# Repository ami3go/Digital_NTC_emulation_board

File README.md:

# Digital_NTC_emulation_board
 Emulation NTC by using digital potentiomener AD5235

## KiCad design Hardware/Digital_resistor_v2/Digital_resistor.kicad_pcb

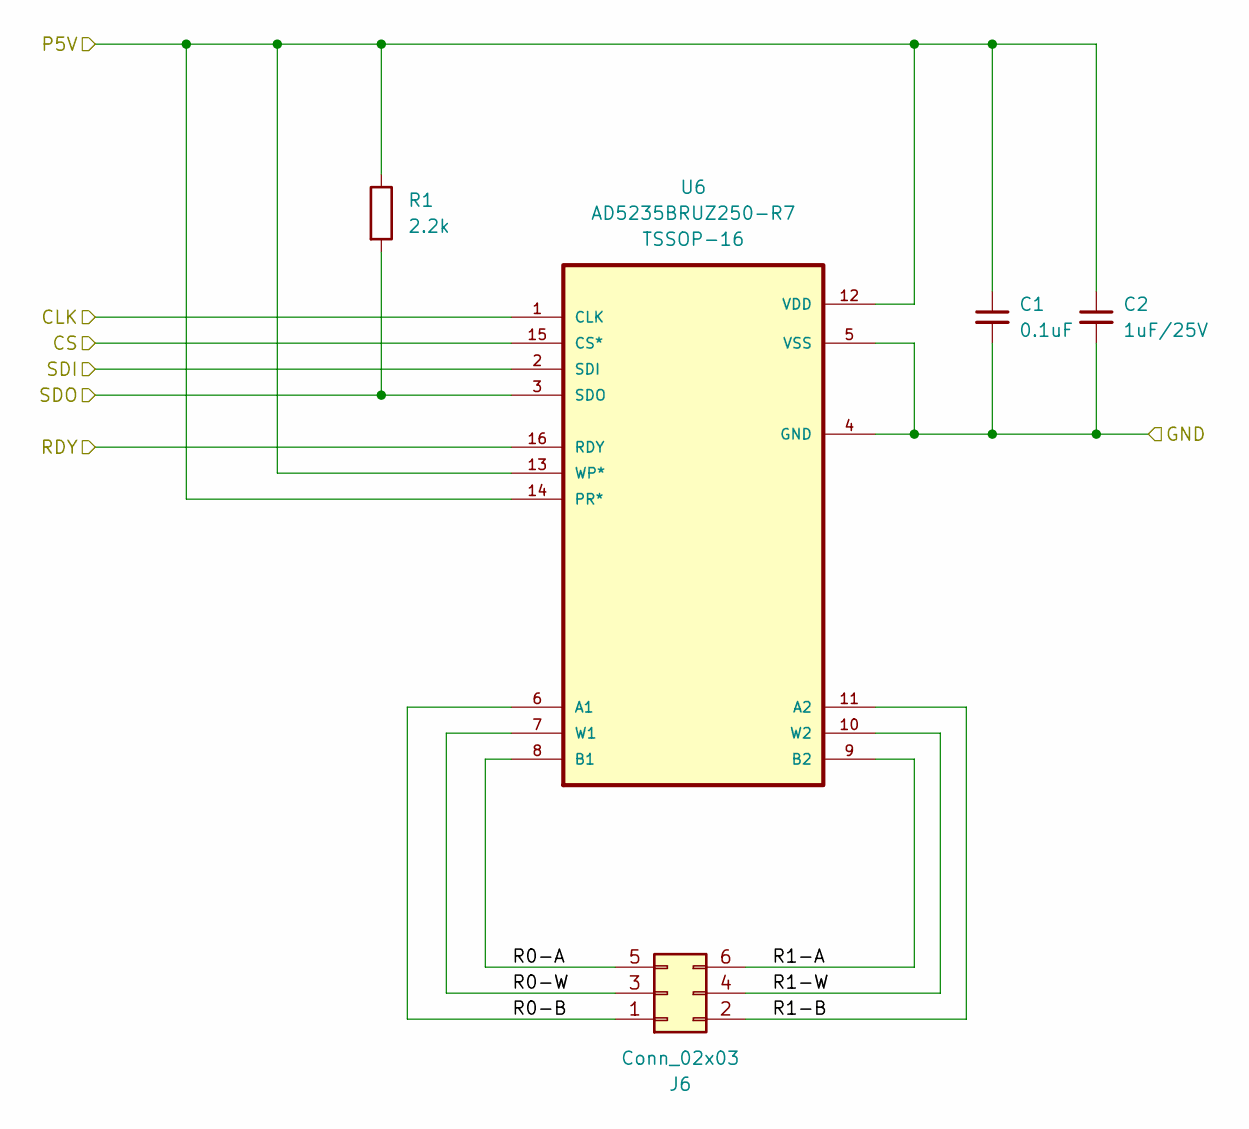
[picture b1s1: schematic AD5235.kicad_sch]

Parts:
C1: 100nF_0603_16V; C_0603; Part Number 0603YC104KAT2A; JLCPCB ID C14663
C2: 1uF_0603_25V; C_0603; Part Number GRM188R61E105KA12D; JLCPCB ID C15849
J6: Conn_02x03; Pins_2x03_2.54mm_TH; Part Number LL1009-2A, 2.54MM 2*3PIN HEADER,LENGTH=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
R1: 2.2k_0603; R_0603; Part Number RC0603FR-072K2L; JLCPCB ID C4190
U6: AD5235BRUZ250-R7; SOP65P640X120-16N; MPN AD5235BRUZ250-R7

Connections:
+5V: C1.1, C2.1, R1.1, U6.12 (VDD), U6.13 (WP*), U6.14 (PR*); also elsewhere on the board
/AD5235-1/R0-A: J6.5 (GND), U6.8 (B1)
/AD5235-1/R0-B: J6.1 (+12V), U6.6 (A1)
/AD5235-1/R0-W: J6.3 (GND), U6.7 (W1)
/AD5235-1/R1-A: J6.6 (GND), U6.9 (B2)
/AD5235-1/R1-B: J6.2 (+12V), U6.11 (A2)
/AD5235-1/R1-W: J6.4 (GND), U6.10 (W2)
/CPU_RP2040-zero/AD_RDY: U6.16 (RDY); also elsewhere on the board
/CPU_RP2040-zero/SPI1_CS: U6.15 (CS*); also elsewhere on the board
/CPU_RP2040-zero/SPI1_SCK: U6.1 (CLK); also elsewhere on the board
/CPU_RP2040-zero/SPI1_TX: U6.2 (SDI); also elsewhere on the board
/SDO1-SDI2: R1.2, U6.3 (SDO); also elsewhere on the board
GND: C1.2, C2.2, U6.4 (GND), U6.5 (VSS); also elsewhere on the board

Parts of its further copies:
C3, C5, C7: 100nF_0603_16V; C_0603; Part Number 0603YC104KAT2A; JLCPCB ID C14663
C4, C6, C8: 1uF_0603_25V; C_0603; Part Number GRM188R61E105KA12D; JLCPCB ID C15849
J0, J2, J4: Conn_02x03; Pins_2x03_2.54mm_TH; Part Number LL1009-2A, 2.54MM 2*3PIN HEADER,LENGTH=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
R2, R3, R4: 2.2k_0603; R_0603; Part Number RC0603FR-072K2L; JLCPCB ID C4190
U0, U2, U4: AD5235BRUZ250-R7; SOP65P640X120-16N; MPN AD5235BRUZ250-R7

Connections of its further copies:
+5V: C3.1, C4.1, C5.1, C6.1, C7.1, C8.1, R2.1, R3.1, R4.1, U0.12 (VDD), U0.13 (WP*), U0.14 (PR*), U2.12 (VDD), U2.13 (WP*), U2.14 (PR*), U4.12 (VDD), U4.13 (WP*), U4.14 (PR*); also elsewhere on the board
/AD5235-2/R0-A: J4.5 (GND), U4.8 (B1)
/AD5235-2/R0-B: J4.1 (+12V), U4.6 (A1)
/AD5235-2/R0-W: J4.3 (GND), U4.7 (W1)
/AD5235-2/R1-A: J4.6 (GND), U4.9 (B2)
/AD5235-2/R1-B: J4.2 (+12V), U4.11 (A2)
/AD5235-2/R1-W: J4.4 (GND), U4.10 (W2)
/AD5235-3/R0-A: J2.5 (GND), U2.8 (B1)
/AD5235-3/R0-B: J2.1 (+12V), U2.6 (A1)
/AD5235-3/R0-W: J2.3 (GND), U2.7 (W1)
/AD5235-3/R1-A: J2.6 (GND), U2.9 (B2)
/AD5235-3/R1-B: J2.2 (+12V), U2.11 (A2)
/AD5235-3/R1-W: J2.4 (GND), U2.10 (W2)
/AD5235-4/R0-A: J0.5 (GND), U0.8 (B1)
/AD5235-4/R0-B: J0.1 (+12V), U0.6 (A1)
/AD5235-4/R0-W: J0.3 (GND), U0.7 (W1)
/AD5235-4/R1-A: J0.6 (GND), U0.9 (B2)
/AD5235-4/R1-B: J0.2 (+12V), U0.11 (A2)
/AD5235-4/R1-W: J0.4 (GND), U0.10 (W2)
/CPU_RP2040-zero/AD_RDY: U0.16 (RDY), U2.16 (RDY), U4.16 (RDY); also elsewhere on the board
/CPU_RP2040-zero/SPI1_CS: U0.15 (CS*), U2.15 (CS*), U4.15 (CS*); also elsewhere on the board
/CPU_RP2040-zero/SPI1_RX: R4.2, U0.3 (SDO); also elsewhere on the board
/CPU_RP2040-zero/SPI1_SCK: U0.1 (CLK), U2.1 (CLK), U4.1 (CLK); also elsewhere on the board
/SDO1-SDI2: U4.2 (SDI); also elsewhere on the board
/SDO2-SDI3: R2.2, U2.2 (SDI), U4.3 (SDO)
/SDO3-SDI4: R3.2, U0.2 (SDI), U2.3 (SDO)
GND: C3.2, C4.2, C5.2, C6.2, C7.2, C8.2, U0.4 (GND), U0.5 (VSS), U2.4 (GND), U2.5 (VSS), U4.4 (GND), U4.5 (VSS); also elsewhere on the board

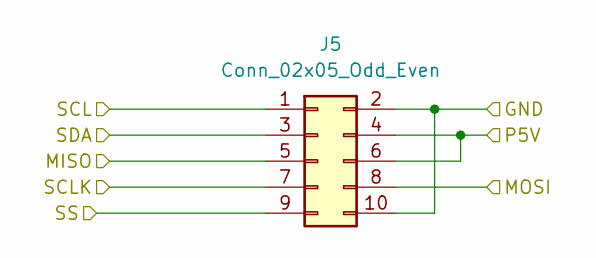
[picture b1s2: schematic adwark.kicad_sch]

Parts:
J5: Conn_02x05_Odd_Even; PinHeader_2x05_P2.54mm_Vertical

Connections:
+5V: J5.4, J5.6; also elsewhere on the board
/CPU_RP2040-zero/SPI1_CS: J5.9; also elsewhere on the board
/CPU_RP2040-zero/SPI1_RX: J5.5; also elsewhere on the board
/CPU_RP2040-zero/SPI1_SCK: J5.7; also elsewhere on the board
/CPU_RP2040-zero/SPI1_TX: J5.8; also elsewhere on the board
/advark_connector/SCL: J5.1
/advark_connector/SDA: J5.3
GND: J5.2, J5.10; also elsewhere on the board

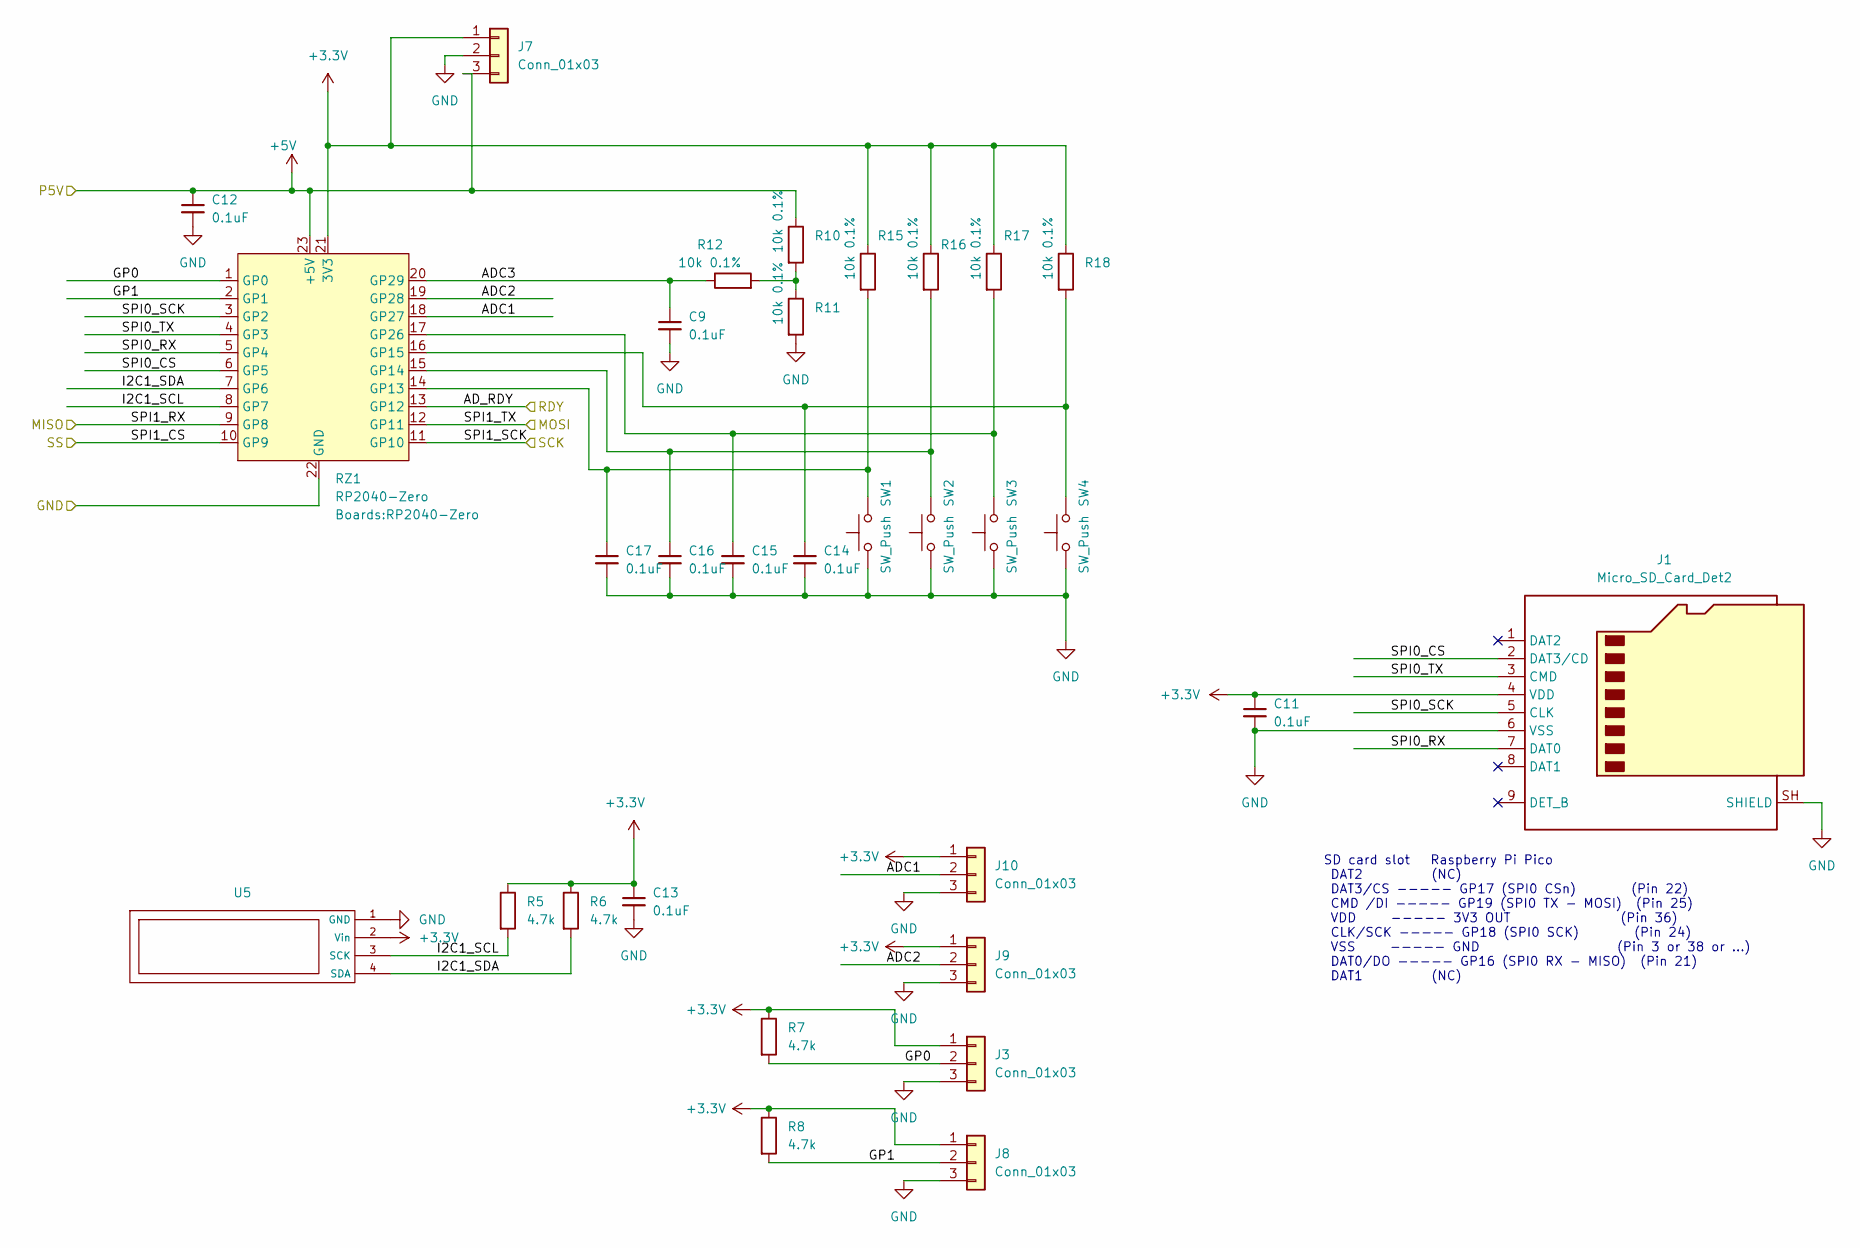
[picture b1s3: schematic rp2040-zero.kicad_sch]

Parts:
C9, C11, C12, C13, C14, C15, C16, C17: 100nF_0603_16V; C_0603; Part Number 0603YC104KAT2A; JLCPCB ID C14663
J1: Micro_SD_Card_Det2; J_SD_Card-micro_socket_A
J3, J7, J8, J9, J10: Conn_01x03; Pins_1x03_2.54mm_TH_AudioInsRGndL; Part Number 1-0301FBV0T
R5, R6, R7, R8: 4.7k_0603; R_0603; Part Number RC0603FR-074K7L; JLCPCB ID C23162
R10, R11, R12, R15, R16, R17, R18: 10k_0603_0.1%; R_0603; Part Number ERJ-PB3B1002V
RZ1: RP2040-Zero
SW1, SW2, SW3, SW4: SW_Push; SW_PUSH_6mm_H4.3mm
U5: SSD1306-0.91-OLED-4pin-128x32

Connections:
+3V3: C11.1, C13.1, J1.4 (VDD), J3.1, J7.1, J8.1, J9.1, J10.1, R5.1, R6.1, R7.1, R8.1, R15.1, R16.1, R17.1, R18.1, RZ1.21 (3V3), U5.2 (Vin)
+5V: C12.1, J7.3, R10.1, RZ1.23 (+5V); also elsewhere on the board
/CPU_RP2040-zero/ADC1: J10.2, RZ1.18 (GP27)
/CPU_RP2040-zero/ADC2: J9.2, RZ1.19 (GP28)
/CPU_RP2040-zero/ADC3: C9.1, R12.1, RZ1.20 (GP29)
/CPU_RP2040-zero/AD_RDY: RZ1.13 (GP12); also elsewhere on the board
/CPU_RP2040-zero/GP0: J3.2, R7.2, RZ1.1 (GP0)
/CPU_RP2040-zero/GP1: J8.2, R8.2, RZ1.2 (GP1)
/CPU_RP2040-zero/I2C1_SCL: R5.2, RZ1.8 (GP7), U5.3 (SCK)
/CPU_RP2040-zero/I2C1_SDA: R6.2, RZ1.7 (GP6), U5.4 (SDA)
/CPU_RP2040-zero/SPI0_CS: J1.2 (DAT3/CD), RZ1.6 (GP5)
/CPU_RP2040-zero/SPI0_RX: J1.7 (DAT0), RZ1.5 (GP4)
/CPU_RP2040-zero/SPI0_SCK: J1.5 (CLK), RZ1.3 (GP2)
/CPU_RP2040-zero/SPI0_TX: J1.3 (CMD), RZ1.4 (GP3)
/CPU_RP2040-zero/SPI1_CS: RZ1.10 (GP9); also elsewhere on the board
/CPU_RP2040-zero/SPI1_RX: RZ1.9 (GP8); also elsewhere on the board
/CPU_RP2040-zero/SPI1_SCK: RZ1.11 (GP10); also elsewhere on the board
/CPU_RP2040-zero/SPI1_TX: RZ1.12 (GP11); also elsewhere on the board
GND: C9.2, C11.2, C12.2, C13.2, C14.2, C15.2, C16.2, C17.2, J1.6 (VSS), J1.SH (SHIELD), J3.3, J7.2, J8.3, J9.3, J10.3, R11.2, RZ1.22 (GND), SW1.1, SW2.1, SW3.1, SW4.1, U5.1 (GND); also elsewhere on the board
unnamed: R10.2, R11.1, R12.2
unnamed: C17.1, R15.2, RZ1.14 (GP13), SW1.2
unnamed: C16.1, R16.2, RZ1.15 (GP14), SW2.2
unnamed: C14.1, R18.2, RZ1.16 (GP15), SW4.2
unnamed: C15.1, R17.2, RZ1.17 (GP26), SW3.2

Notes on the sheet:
SD card slot Raspberry Pi Pico DAT2 (NC) DAT3/CS ----- GP17 (SPI0 CSn) (Pin 22) CMD /DI ----- GP19 (SPI0 TX - MOSI) (Pin 25) VDD ----- 3V3 OUT (Pin 36) CLK/SCK ----- GP18 (SPI0 SCK) (Pin 24) VSS ----- GND (Pin 3 or 38 or ...) DAT0/DO ----- GP16 (SPI0 RX - MISO) (Pin 21) DAT1 (NC)

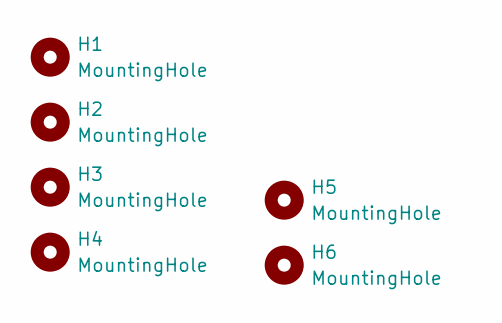
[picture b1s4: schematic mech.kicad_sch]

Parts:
H1, H2, H3, H4, H5, H6: MountingHole; MountingHole_3.2mm_M3_ISO14580

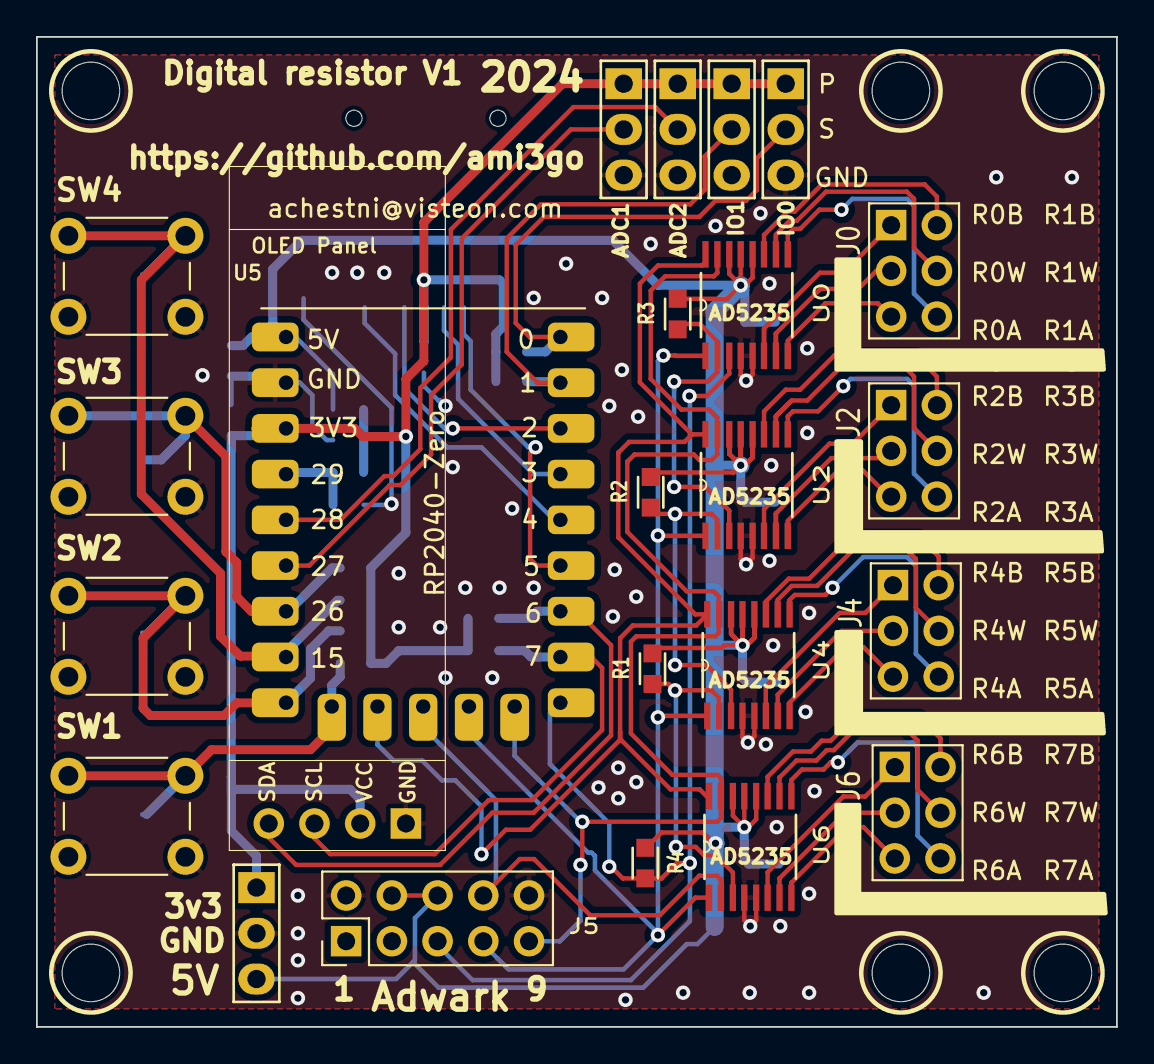
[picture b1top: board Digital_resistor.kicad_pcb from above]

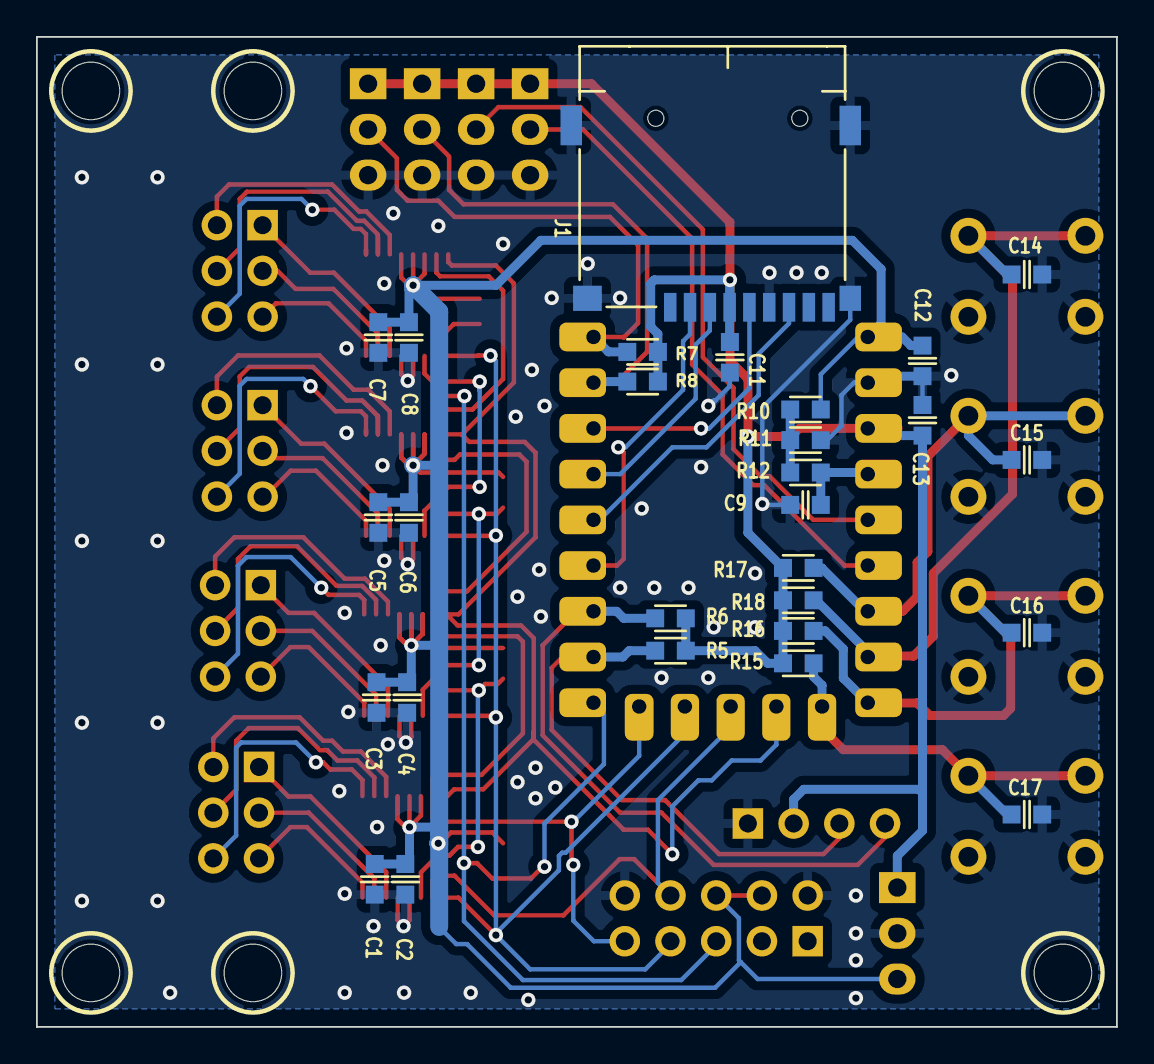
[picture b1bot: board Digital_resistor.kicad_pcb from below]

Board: 2 copper layers, 60.0 x 55.0 mm, 58 parts (28 on the bottom side), 51 nets.

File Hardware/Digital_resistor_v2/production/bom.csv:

Designator,Footprint,Quantity,Value,LCSC Part #
"C1, C11, C12, C13, C14, C15, C16, C17, C3, C5, C7, C9",C_0603,12,100nF_0603_16V,
"C2, C4, C6, C8",C_0603,4,1uF_0603_25V,
"H1, H2, H3, H4, H5, H6",MountingHole_3.2mm_M3_ISO14580,6,MountingHole,
"J0, J2, J4, J6",Pins_2x03_2.54mm_TH,4,Conn_02x03,
J1,J_SD_Card-micro_socket_A,1,Micro_SD_Card_Det2,
"J10, J3, J7, J8, J9",Pins_1x03_2.54mm_TH_AudioInsRGndL,5,Conn_01x03,
J5,PinHeader_2x05_P2.54mm_Vertical,1,Conn_02x05_Odd_Even,
"R1, R2, R3, R4",R_0603,4,2.2k_0603,
"R10, R11, R12, R15, R16, R17, R18",R_0603,7,10k_0603_0.1%,
"R5, R6, R7, R8",R_0603,4,4.7k_0603,
RZ1,RP2040-Zero,1,RP2040-Zero,
"SW1, SW2, SW3, SW4",SW_PUSH_6mm_H4.3mm,4,SW_Push,
"U0, U2, U4, U6",SOP65P640X120-16N,4,AD5235BRUZ250-R7,AD5235BRUZ250-R7
U5,SSD1306-0.91-OLED-4pin-128x32,1,~,

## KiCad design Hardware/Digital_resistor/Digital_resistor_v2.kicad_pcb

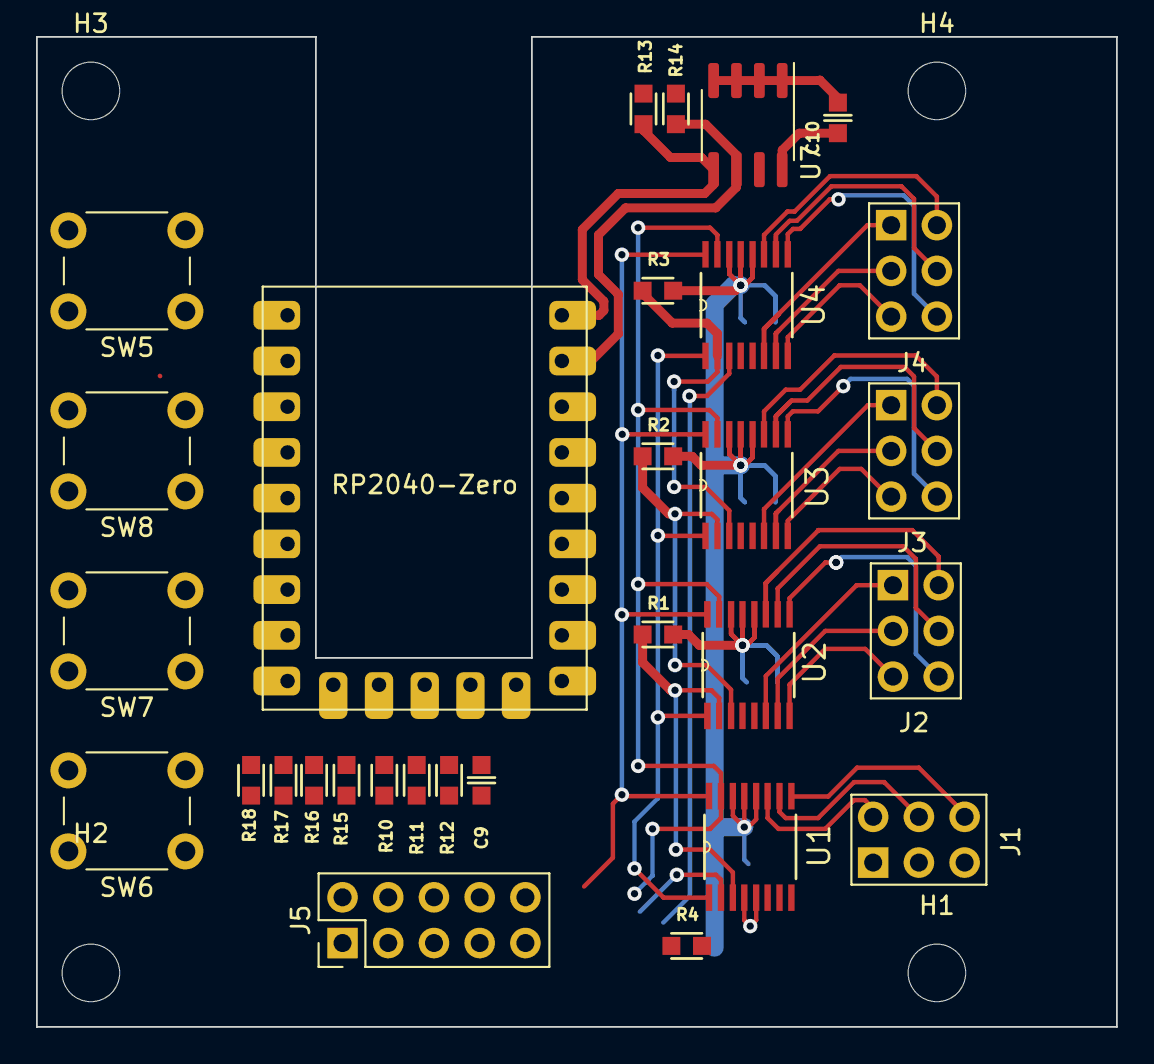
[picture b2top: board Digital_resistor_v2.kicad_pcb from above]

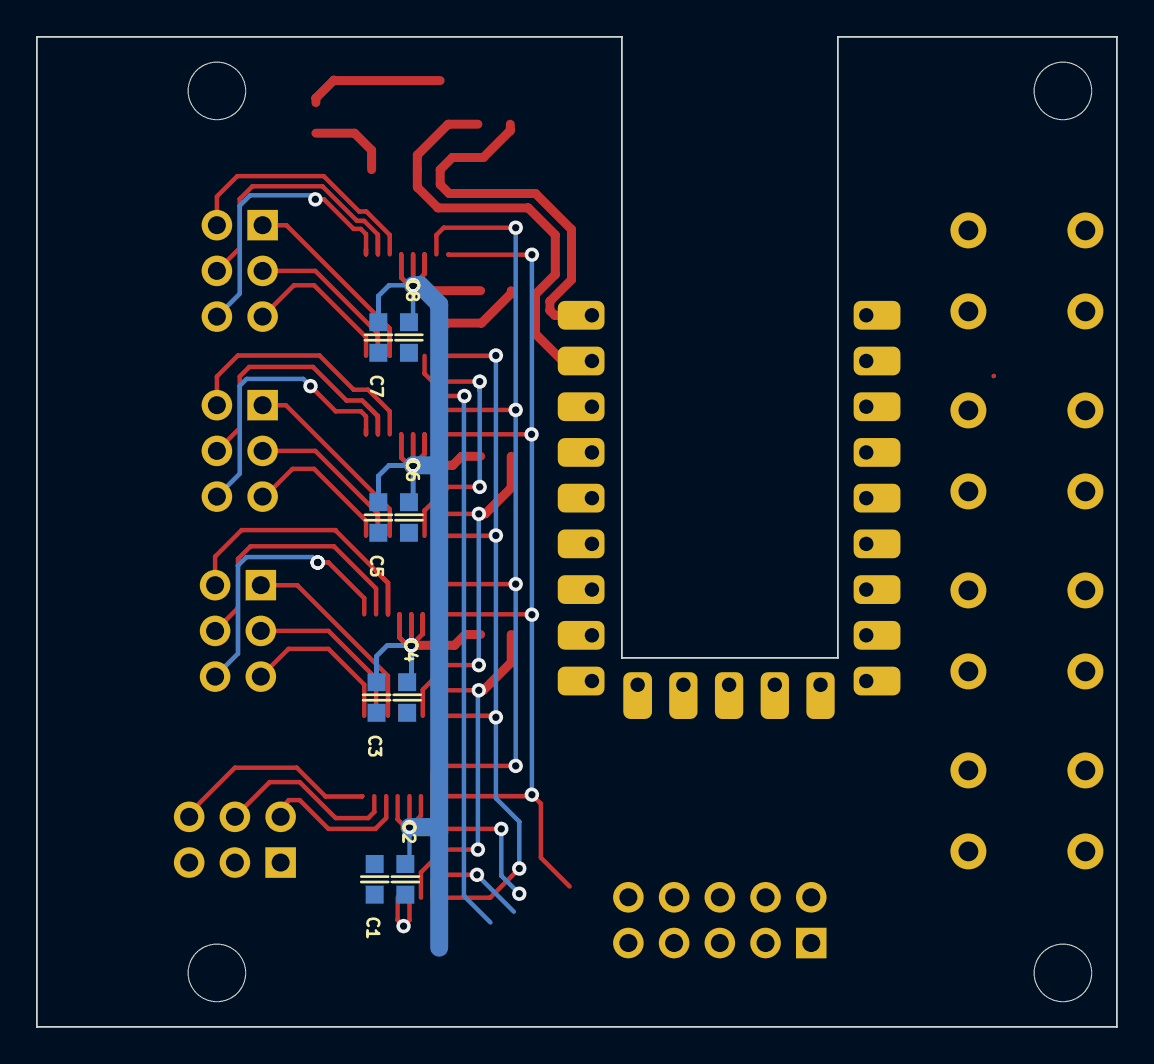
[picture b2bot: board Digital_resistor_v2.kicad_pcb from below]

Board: 2 copper layers, 60.0 x 55.0 mm, 42 parts (8 on the bottom side), 43 nets.

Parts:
C1, C3, C5, C7, C9, C10: 100nF_0603_16V; C_0603
C2, C4, C6, C8: 1uF_0603_25V; C_0603
H1, H2, H3, H4: MountingHole; MountingHole_3.2mm_M3_ISO14580
J1, J2, J3, J4: Conn_02x03; Pins_2x03_2.54mm_TH
J5: Conn_02x05_Odd_Even; PinHeader_2x05_P2.54mm_Vertical
R1, R2, R3, R4: 2.2k_0603; R_0603
R10, R11, R12, R15, R16, R17, R18: 10k_0603_0.1%; R_0603
R13, R14: 4.7k_0603; R_0603
RZ1: RP2040-Zero
SW5, SW6, SW7, SW8: SW_Push; SW_PUSH_6mm_H4.3mm
U1, U2, U3, U4: AD5235BRUZ250-R7; SOP65P640X120-16N
U7: M24C02-WMN; SOIC-8_3.9x4.9mm_P1.27mm

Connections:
+3V3: C10.1, R13.1, R14.1, R15.1, R16.1, R17.1, R18.1, RZ1.21 (3V3), U7.8 (VCC)
+5V: C1.1, C2.1, C3.1, C4.1, C5.1, C6.1, C7.1, C8.1, J5.4, J5.6, R1.1, R2.1, R3.1, R4.1, R10.1, RZ1.22 (5V), U1.12 (VDD), U1.13 (WP*), U1.14 (PR*), U2.12 (VDD), U2.13 (WP*), U2.14 (PR*), U3.12 (VDD), U3.13 (WP*), U3.14 (PR*), U4.12 (VDD), U4.13 (WP*), U4.14 (PR*)
/AD5235-1/SDO: R1.2, U1.3 (SDO), U2.2 (SDI)
/AD5235-2/SDO: R2.2, U2.3 (SDO), U3.2 (SDI)
/AD5235-3/SDO: R3.2, U3.3 (SDO), U4.2 (SDI)
/CPU_RP2040-zero/AD_RDY: RZ1.8 (GP7), U1.16 (RDY), U2.16 (RDY), U3.16 (RDY), U4.16 (RDY)
/CPU_RP2040-zero/I2C0_SCL: R14.2, RZ1.2 (GP1), U7.6 (SCL)
/CPU_RP2040-zero/I2C0_SDA: R13.2, RZ1.1 (GP0), U7.5 (SDA)
/CPU_RP2040-zero/SPI0_CS: J5.9, RZ1.6 (GP5), U1.15 (CS*), U2.15 (CS*), U3.15 (CS*), U4.15 (CS*)
/CPU_RP2040-zero/SPI0_RX: J5.8, RZ1.5 (GP4), U1.2 (SDI)
/CPU_RP2040-zero/SPI0_SCK: J5.7, RZ1.7 (GP6), U1.1 (CLK), U2.1 (CLK), U3.1 (CLK), U4.1 (CLK)
/CPU_RP2040-zero/SPI0_TX: J5.5, R4.2, RZ1.4 (GP3), U4.3 (SDO)
GND: C1.2, C2.2, C3.2, C4.2, C5.2, C6.2, C7.2, C8.2, C9.2, C10.2, J5.2, J5.10, R11.2, SW5.1, SW6.1, SW7.1, SW8.1, U1.4 (GND), U1.5 (VSS), U2.4 (GND), U2.5 (VSS), U3.4 (GND), U3.5 (VSS), U4.4 (GND), U4.5 (VSS), U7.1 (E0), U7.2 (E1), U7.3 (E2), U7.4 (VSS)
unnamed: R10.2, R11.1, R12.2
unnamed: R15.2, RZ1.15 (GP14), SW5.2
unnamed: R16.2, RZ1.16 (GP15), SW6.2
unnamed: R17.2, RZ1.17 (GP26), SW7.2
unnamed: R18.2, RZ1.18 (GP27), SW8.2
unnamed: C9.1, R12.1, RZ1.20 (GP29)
unnamed: J1.1 (+12V), U1.6 (A1)
unnamed: J1.2 (+12V), U1.11 (A2)
unnamed: J1.5 (GND), U1.8 (B1)
unnamed: J1.6 (GND), U1.9 (B2)
unnamed: J1.3 (GND), U1.7 (W1)
unnamed: J1.4 (GND), U1.10 (W2)
unnamed: J2.1 (+12V), U2.6 (A1)
unnamed: J2.2 (+12V), U2.11 (A2)
unnamed: J2.5 (GND), U2.8 (B1)
unnamed: J2.6 (GND), U2.9 (B2)
unnamed: J2.3 (GND), U2.7 (W1)
unnamed: J2.4 (GND), U2.10 (W2)
unnamed: J3.1 (+12V), U3.6 (A1)
unnamed: J3.2 (+12V), U3.11 (A2)
unnamed: J3.5 (GND), U3.8 (B1)
unnamed: J3.6 (GND), U3.9 (B2)
unnamed: J3.3 (GND), U3.7 (W1)
unnamed: J3.4 (GND), U3.10 (W2)
unnamed: J4.1 (+12V), U4.6 (A1)
unnamed: J4.2 (+12V), U4.11 (A2)
unnamed: J4.5 (GND), U4.8 (B1)
unnamed: J4.6 (GND), U4.9 (B2)
unnamed: J4.3 (GND), U4.7 (W1)
unnamed: J4.4 (GND), U4.10 (W2)

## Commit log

2024-01-12 update structure
2024-01-12 working of FSM
    FSM states and traditions need to be defined
2024-01-15 change arduino nano to RP2040-Zero
2024-01-21 finish layout
2024-01-21 Added Gerbers
2024-01-21 working on AD5235 driver
2024-01-21 reposition firmware folders
2024-01-21 configure pycharm
2024-01-22 added HW v2
    V2 change list:
    - removed EERPROM as RP2040-Zero Have 2 Mbyte flash which can store user files as well
    - Added 2 ADCs for general purpose
    - Added 2 GPIOs for general purpose. could be used with DS18B20
2024-01-23 Create cli_ai_gen_v4
2024-01-23 Rename cli_ai_gen_v4 to cli_ai_gen_v4.py
2024-01-23 remove submodule and keep one git repo
2024-01-23 Added AD5235.drawio
2024-01-25 apdated AD5235
2024-01-25 other updates
2024-01-27 CLI lib update
2024-01-27 CLI lib update names
2024-01-27 first working CLI on RP2040
2024-01-27 first working CLI on RP2040 with uasyncio
2024-02-03 pdf update
2024-02-10 AD5235 drive update working
2024-02-10 AD5235 drive update optimize drive
2024-02-10 change write_to_dev to write Add get_res
2024-02-10 send box update
2024-02-10 autosave update
2024-02-13 capture working state
2024-02-15 non bloking USB uart reading. Need a bit more work bit workign for now with some rundom crashes
2024-02-19 added check for empty string. move cli task to separated file
2024-02-20 small update to: CLI AD5235
2024-02-20 git ignore
2024-02-21 clean up project
    clean up project
